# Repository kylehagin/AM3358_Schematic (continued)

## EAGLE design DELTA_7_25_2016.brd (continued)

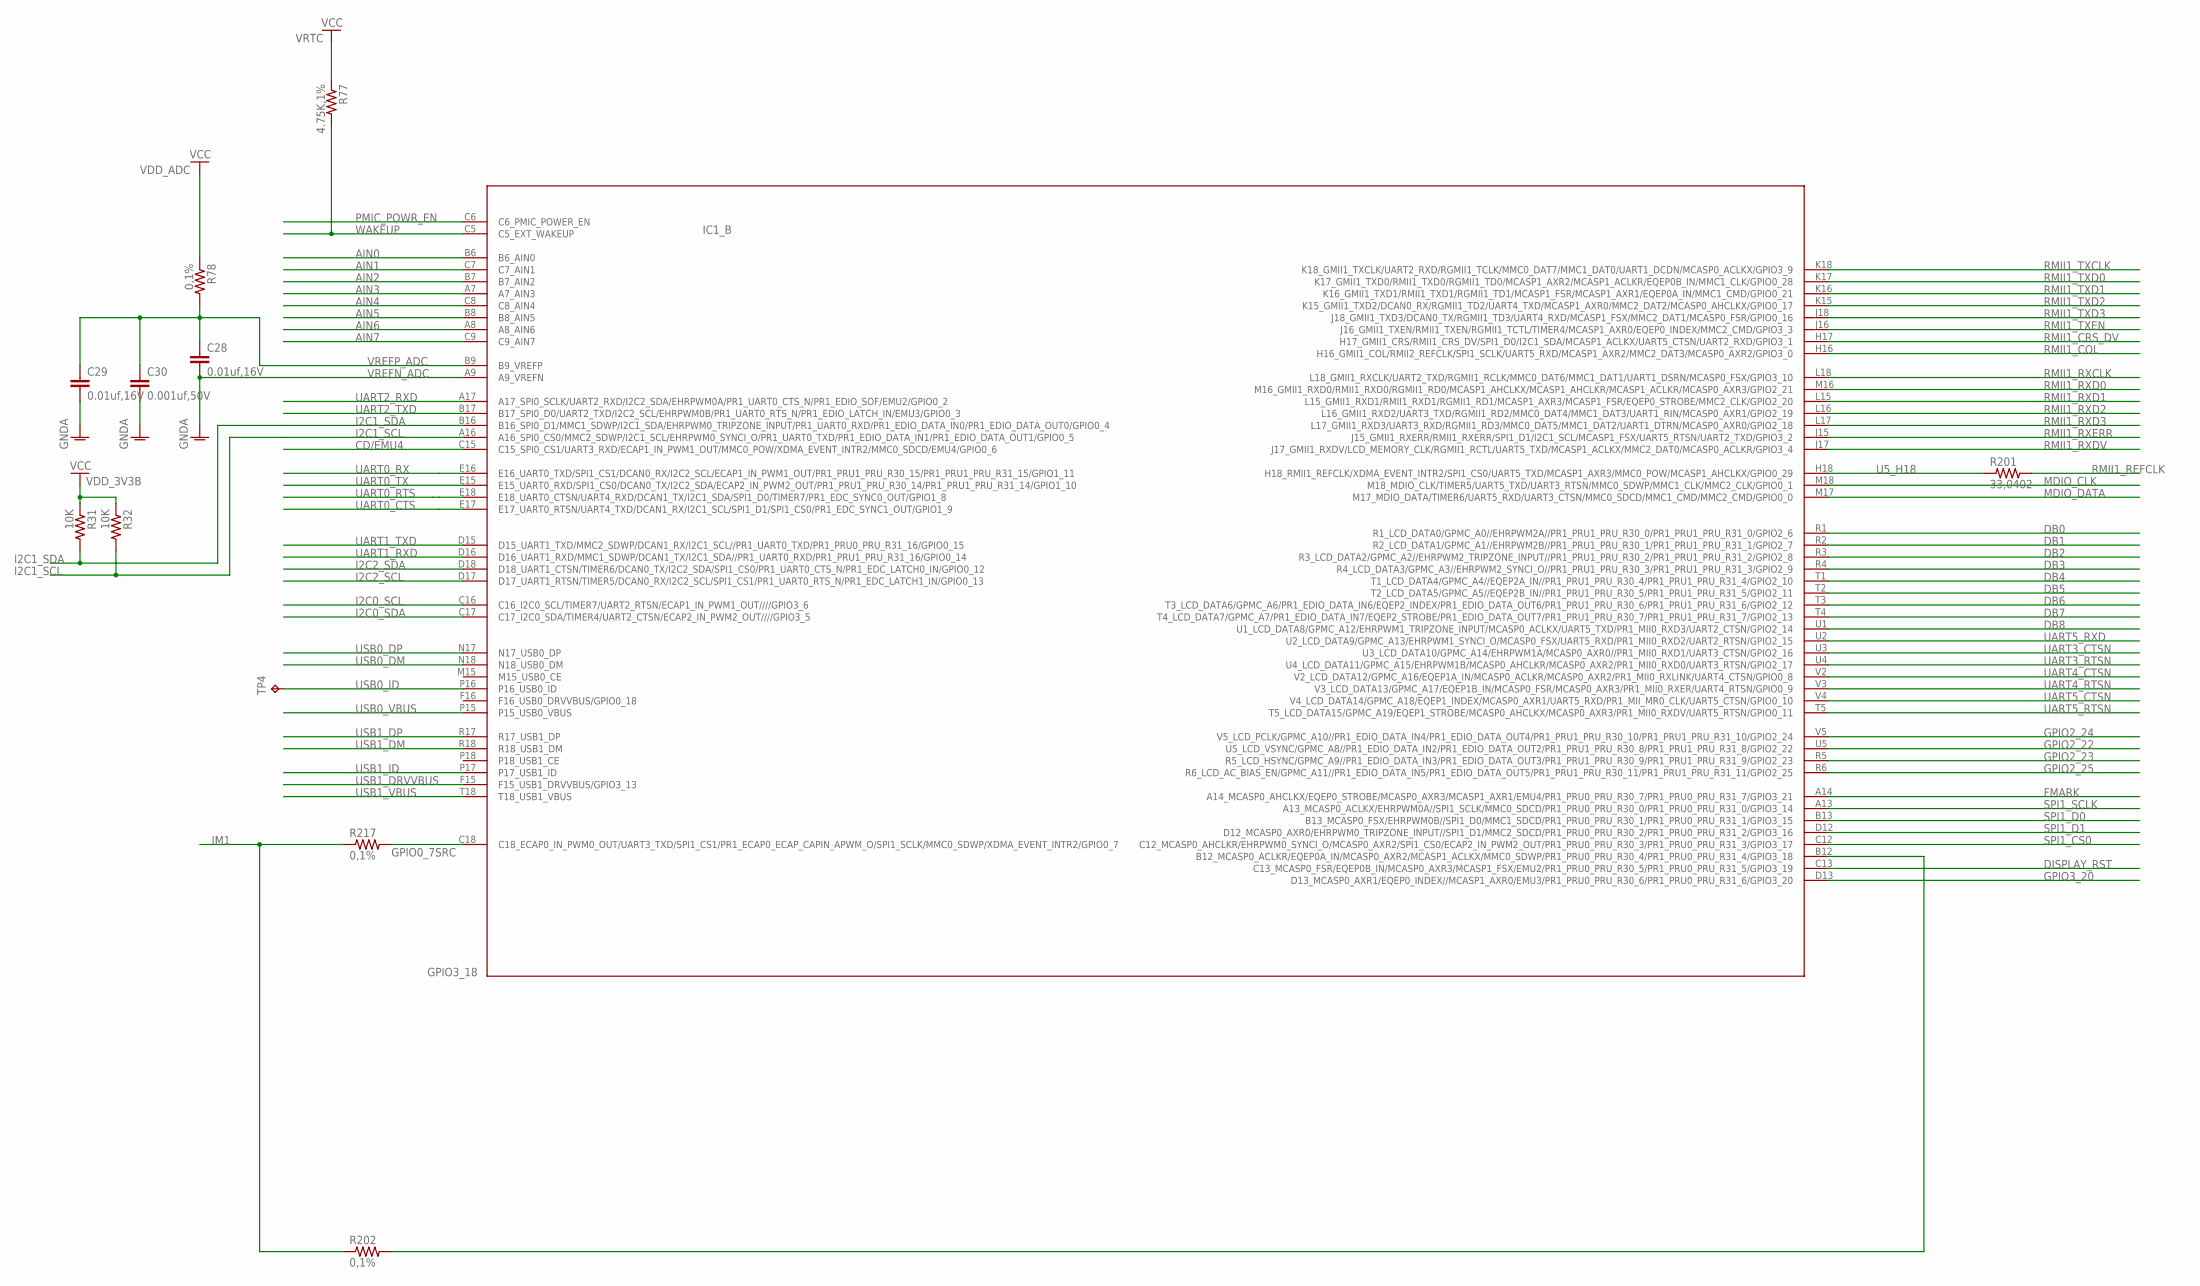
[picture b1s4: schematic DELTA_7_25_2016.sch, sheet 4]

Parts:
C28, C29: 0.01uf,16V; C0402
C30: 0.001uf,50V; C0402
IC1: AM335X_ZCZ; ZCZ_S-PBGA-N324
R31, R32: 10K; R0402
R77: 4.75K,1%; R0402
R78, R202, R217: 0,1%; R0402
R201: 33,0402; R0402
TP4: TPB1,27; B1,27

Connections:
AIN0: IC1.B6 (B6_AIN0); also elsewhere on the board
AIN1: IC1.C7 (C7_AIN1); also elsewhere on the board
AIN2: IC1.B7 (B7_AIN2); also elsewhere on the board
AIN3: IC1.A7 (A7_AIN3); also elsewhere on the board
AIN4: IC1.C8 (C8_AIN4); also elsewhere on the board
AIN5: IC1.B8 (B8_AIN5); also elsewhere on the board
AIN6: IC1.A8 (A8_AIN6); also elsewhere on the board
AIN7: IC1.C9 (C9_AIN7); also elsewhere on the board
CD/EMU4: IC1.C15 (C15_SPI0_CS1/UART3_RXD/ECAP1_IN_PWM1_OU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); also elsewhere on the board
DB0: IC1.R1 (R1_LCD_DATA0/GPMC_A0//EHRPWM2A//PR1_PRU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); also elsewhere on the board
DB1: IC1.R2 (R2_LCD_DATA1/GPMC_A1//EHRPWM2B//PR1_PRU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); also elsewhere on the board
DB2: IC1.R3 (R3_LCD_DATA2/GPMC_A2//EHRPWM2_TRIPZONE_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); also elsewhere on the board
DB3: IC1.R4 (R4_LCD_DATA3/GPMC_A3//EHRPWM2_SYNCI_O//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); also elsewhere on the board
DB4: IC1.T1 (T1_LCD_DATA4/GPMC_A4//EQEP2A_IN//PR1_PR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); also elsewhere on the board
DB5: IC1.T2 (T2_LCD_DATA5/GPMC_A5//EQEP2B_IN//PR1_PR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); also elsewhere on the board
DB6: IC1.T3 (T3_LCD_DATA6/GPMC_A6/PR1_EDIO_DATA_IN6/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); also elsewhere on the board
DB7: IC1.T4 (T4_LCD_DATA7/GPMC_A7/PR1_EDIO_DATA_IN7/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); also elsewhere on the board
DB8: IC1.U1 (U1_LCD_DATA8/GPMC_A12/EHRPWM1_TRIPZONE_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); also elsewhere on the board
DISPLAY_RST: IC1.C13 (C13_MCASP0_FSR/EQEP0B_IN/MCASP0_AXR3/MC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); also elsewhere on the board
FMARK: IC1.A14 (A14_MCASP0_AHCLKX/EQEP0_STROBE/MCASP0_A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); also elsewhere on the board
GNDA: C29.2, C30.2; also elsewhere on the board
GPIO0_7SRC: IC1.C18 (C18_ECAP0_IN_PWM0_OUT/UART3_TXD/SPI1_CS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), R217.2
GPIO2_22: IC1.U5 (U5_LCD_VSYNC/GPMC_A8//PR1_EDIO_DATA_IN2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); also elsewhere on the board
GPIO2_23: IC1.R5 (R5_LCD_HSYNC/GPMC_A9//PR1_EDIO_DATA_IN3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); also elsewhere on the board
GPIO2_24: IC1.V5 (V5_LCD_PCLK/GPMC_A10//PR1_EDIO_DATA_IN4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); also elsewhere on the board
GPIO2_25: IC1.R6 (R6_LCD_AC_BIAS_EN/GPMC_A11//PR1_EDIO_DA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); also elsewhere on the board
GPIO3_18: IC1.B12 (B12_MCASP0_ACLKR/EQEP0A_IN/MCASP0_AXR2/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), R202.2
GPIO3_20: IC1.D13 (D13_MCASP0_AXR1/EQEP0_INDEX//MCASP1_AXR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); also elsewhere on the board
I2C0_SCL: IC1.C16 (C16_I2C0_SCL/TIMER7/UART2_RTSN/ECAP1_IN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); also elsewhere on the board
I2C0_SDA: IC1.C17 (C17_I2C0_SDA/TIMER4/UART2_CTSN/ECAP2_IN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); also elsewhere on the board
I2C1_SCL: IC1.A16 (A16_SPI0_CS0/MMC2_SDWP/I2C1_SCL/EHRPWM0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), R32.2; also elsewhere on the board
I2C1_SDA: IC1.B16 (B16_SPI0_D1/MMC1_SDWP/I2C1_SDA/EHRPWM0_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), R31.2; also elsewhere on the board
I2C2_SCL: IC1.D17 (D17_UART1_RTSN/TIMER5/DCAN0_RX/I2C2_SCL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); also elsewhere on the board
I2C2_SDA: IC1.D18 (D18_UART1_CTSN/TIMER6/DCAN0_TX/I2C2_SDA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); also elsewhere on the board
IM1: R202.1, R217.1; also elsewhere on the board
MDIO_CLK: IC1.M18 (M18_MDIO_CLK/TIMER5/UART5_TXD/UART3_RTS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); also elsewhere on the board
MDIO_DATA: IC1.M17 (M17_MDIO_DATA/TIMER6/UART5_RXD/UART3_CT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); also elsewhere on the board
PMIC_POWR_EN: IC1.C6 (C6_PMIC_POWER_EN); also elsewhere on the board
RMII1_COL: IC1.H16 (H16_GMII1_COL/RMII2_REFCLK/SPI1_SCLK/UA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); also elsewhere on the board
RMII1_CRS_DV: IC1.H17 (H17_GMII1_CRS/RMII1_CRS_DV/SPI1_D0/I2C1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); also elsewhere on the board
RMII1_REFCLK: R201.2; also elsewhere on the board
RMII1_RXCLK: IC1.L18 (L18_GMII1_RXCLK/UART2_TXD/RGMII1_RCLK/M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); also elsewhere on the board
RMII1_RXD0: IC1.M16 (M16_GMII1_RXD0/RMII1_RXD0/RGMII1_RD0/MC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); also elsewhere on the board
RMII1_RXD1: IC1.L15 (L15_GMII1_RXD1/RMII1_RXD1/RGMII1_RD1/MC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); also elsewhere on the board
RMII1_RXD2: IC1.L16 (L16_GMII1_RXD2/UART3_TXD/RGMII1_RD2/MMC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); also elsewhere on the board
RMII1_RXD3: IC1.L17 (L17_GMII1_RXD3/UART3_RXD/RGMII1_RD3/MMC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); also elsewhere on the board
RMII1_RXDV: IC1.J17 (J17_GMII1_RXDV/LCD_MEMORY_CLK/RGMII1_RC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); also elsewhere on the board
RMII1_RXERR: IC1.J15 (J15_GMII1_RXERR/RMII1_RXERR/SPI1_D1/I2C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); also elsewhere on the board
RMII1_TXCLK: IC1.K18 (K18_GMII1_TXCLK/UART2_RXD/RGMII1_TCLK/M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); also elsewhere on the board
RMII1_TXD0: IC1.K17 (K17_GMII1_TXD0/RMII1_TXD0/RGMII1_TD0/MC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); also elsewhere on the board
RMII1_TXD1: IC1.K16 (K16_GMII1_TXD1/RMII1_TXD1/RGMII1_TD1/MC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); also elsewhere on the board
RMII1_TXD2: IC1.K15 (K15_GMII1_TXD2/DCAN0_RX/RGMII1_TD2/UART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); also elsewhere on the board
RMII1_TXD3: IC1.J18 (J18_GMII1_TXD3/DCAN0_TX/RGMII1_TD3/UART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); also elsewhere on the board
RMII1_TXEN: IC1.J16 (J16_GMII1_TXEN/RMII1_TXEN/RGMII1_TCTL/T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); also elsewhere on the board
SPI1_CS0: IC1.C12 (C12_MCASP0_AHCLKR/EHRPWM0_SYNCI_O/MCASP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); also elsewhere on the board
SPI1_D0: IC1.B13 (B13_MCASP0_FSX/EHRPWM0B//SPI1_D0/MMC1_S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); also elsewhere on the board
SPI1_D1: IC1.D12 (D12_MCASP0_AXR0/EHRPWM0_TRIPZONE_INPUT/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); also elsewhere on the board
SPI1_SCLK: IC1.A13 (A13_MCASP0_ACLKX/EHRPWM0A//SPI1_SCLK/MM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); also elsewhere on the board
U5_H18: IC1.H18 (H18_RMII1_REFCLK/XDMA_EVENT_INTR2/SPI1_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), R201.1
UART0_CTS: IC1.E17 (E17_UART0_RTSN/UART4_TXD/DCAN1_RX/I2C1_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); also elsewhere on the board
UART0_RTS: IC1.E18 (E18_UART0_CTSN/UART4_RXD/DCAN1_TX/I2C1_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); also elsewhere on the board
UART0_RX: IC1.E16 (E16_UART0_TXD/SPI1_CS1/DCAN0_RX/I2C2_SC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); also elsewhere on the board
UART0_TX: IC1.E15 (E15_UART0_RXD/SPI1_CS0/DCAN0_TX/I2C2_SD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); also elsewhere on the board
UART1_RXD: IC1.D16 (D16_UART1_RXD/MMC1_SDWP/DCAN1_TX/I2C1_S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); also elsewhere on the board
UART1_TXD: IC1.D15 (D15_UART1_TXD/MMC2_SDWP/DCAN1_RX/I2C1_S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); also elsewhere on the board
UART2_RXD: IC1.A17 (A17_SPI0_SCLK/UART2_RXD/I2C2_SDA/EHRPWM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); also elsewhere on the board
UART2_TXD: IC1.B17 (B17_SPI0_D0/UART2_TXD/I2C2_SCL/EHRPWM0B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); also elsewhere on the board
UART3_CTSN: IC1.U3 (U3_LCD_DATA10/GPMC_A14/EHRPWM1A/MCASP0_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); also elsewhere on the board
UART3_RTSN: IC1.U4 (U4_LCD_DATA11/GPMC_A15/EHRPWM1B/MCASP0_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); also elsewhere on the board
UART4_CTSN: IC1.V2 (V2_LCD_DATA12/GPMC_A16/EQEP1A_IN/MCASP0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); also elsewhere on the board
UART4_RTSN: IC1.V3 (V3_LCD_DATA13/GPMC_A17/EQEP1B_IN/MCASP0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); also elsewhere on the board
UART5_CTSN: IC1.V4 (V4_LCD_DATA14/GPMC_A18/EQEP1_INDEX/MCAS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); also elsewhere on the board
UART5_RTSN: IC1.T5 (T5_LCD_DATA15/GPMC_A19/EQEP1_STROBE/MCA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); also elsewhere on the board
UART5_RXD: IC1.U2 (U2_LCD_DATA9/GPMC_A13/EHRPWM1_SYNCI_O/M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); also elsewhere on the board
USB0_DM: IC1.N18 (N18_USB0_DM); also elsewhere on the board
USB0_DP: IC1.N17 (N17_USB0_DP); also elsewhere on the board
USB0_ID: IC1.P16 (P16_USB0_ID), TP4.TP
USB0_VBUS: IC1.P15 (P15_USB0_VBUS); also elsewhere on the board
USB1_DM: IC1.R18 (R18_USB1_DM); also elsewhere on the board
USB1_DP: IC1.R17 (R17_USB1_DP); also elsewhere on the board
USB1_DRVVBUS: IC1.F15 (F15_USB1_DRVVBUS/GPIO3_13); also elsewhere on the board
USB1_ID: IC1.P17 (P17_USB1_ID); also elsewhere on the board
USB1_VBUS: IC1.T18 (T18_USB1_VBUS); also elsewhere on the board
VDD_3V3B: R31.1, R32.1; also elsewhere on the board
VDD_ADC: R78.1; also elsewhere on the board
VREFN_ADC: C28.2, IC1.A9 (A9_VREFN)
VREFP_ADC: C28.1, C29.1, C30.1, IC1.B9 (B9_VREFP), R78.2
VRTC: R77.1; also elsewhere on the board
WAKEUP: IC1.C5 (C5_EXT_WAKEUP), R77.2; also elsewhere on the board

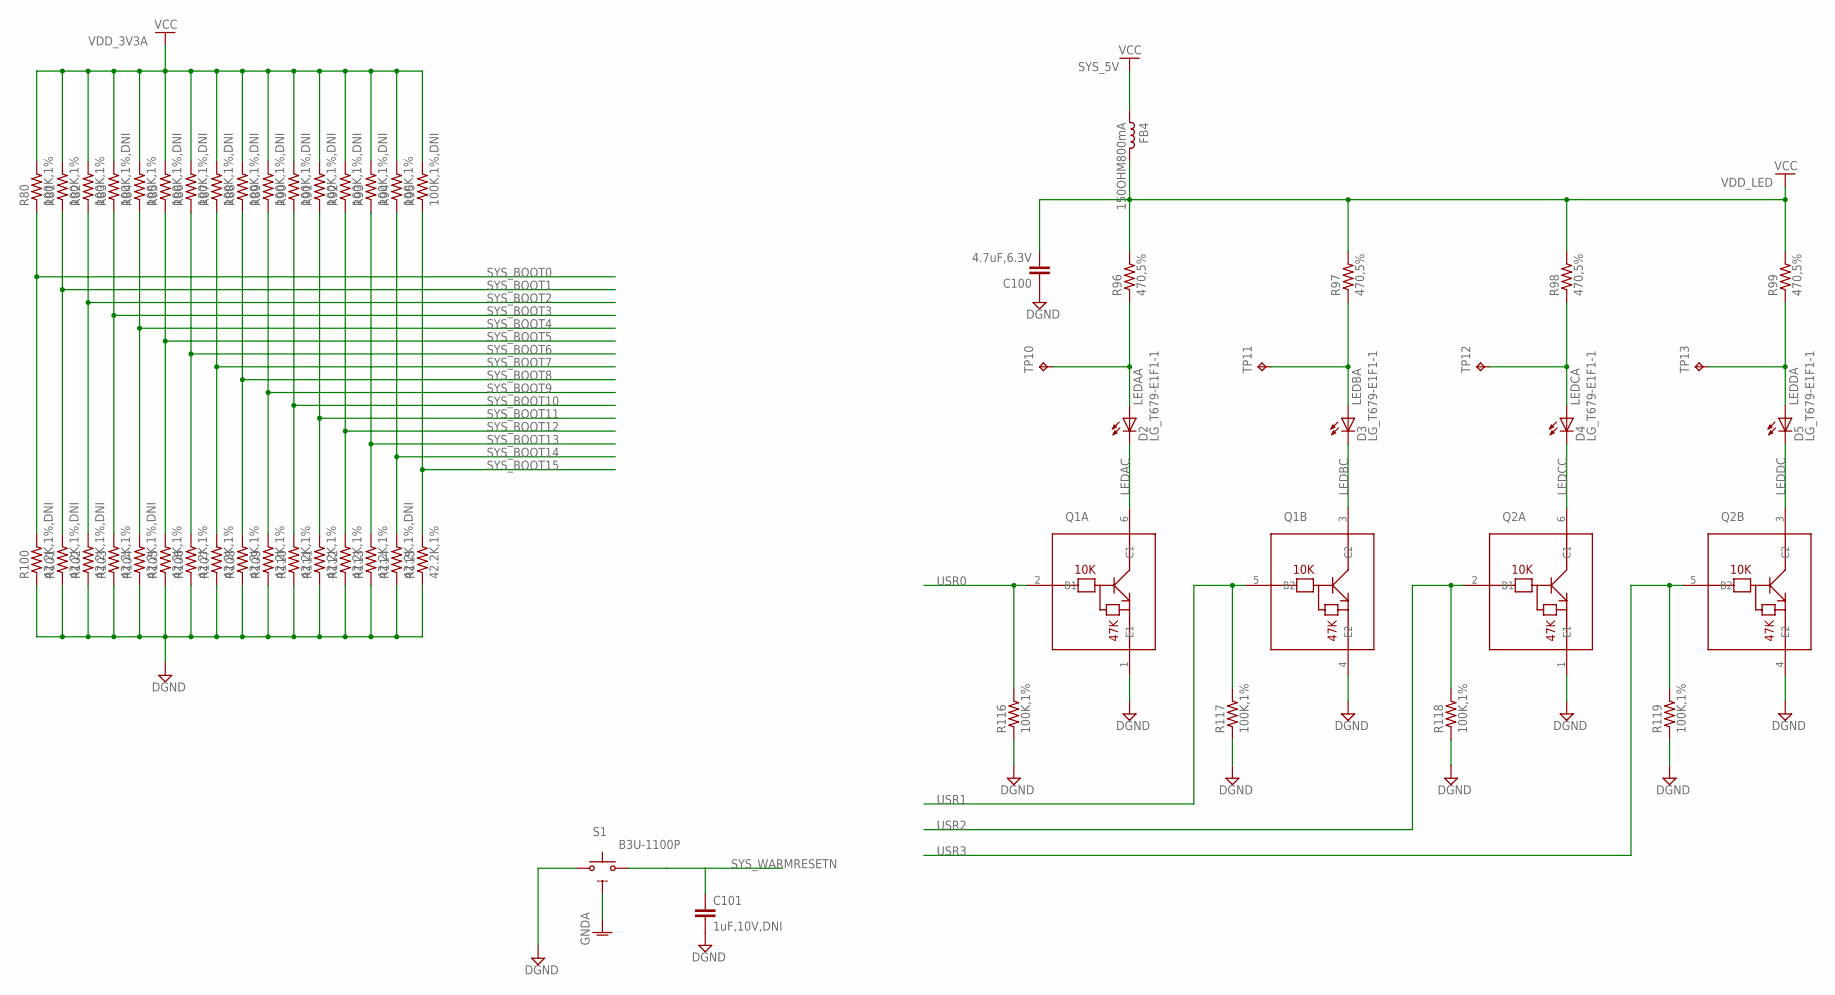
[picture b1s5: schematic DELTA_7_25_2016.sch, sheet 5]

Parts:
C100: 4.7uF,6.3V; C0402
C101: 1uF,10V,DNI; C0805
D2, D3, D4, D5: LG_T679-E1F1-1; PLCC2
FB4: 150OHM800mA; L0603
Q1, Q2: DMC56404
R80, R81, R82, R84, R94, R116, R117, R118, R119: 100K,1%; R0402
R83, R85, R86, R87, R88, R89, R90, R91, R92, R93, R95: 100K,1%,DNI; R0402
R96, R97, R98, R99: 470,5%; R0402
R100, R101, R102, R104, R114: 42.2K,1%,DNI; R0402
R103, R105, R106, R107, R108, R109, R110, R111, R112, R113, R115: 42.2K,1%; R0402
S1: B3U-1100P
TP10, TP11, TP12, TP13: TPB1,27; B1,27

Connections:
DGND: C100.1, C101.2, Q1.1 (E1), Q1.4 (E2), Q2.1 (E1), Q2.4 (E2), R100.1, R101.1, R102.1, R103.1, R104.1, R105.1, R106.1, R107.1, R108.1, R109.1, R110.1, R111.1, R112.1, R113.1, R114.1, R115.1, R116.1, R117.1, R118.1, R119.1, S1.1; also elsewhere on the board
GNDA: S1.S (G); also elsewhere on the board
LEDAA: D2.A, R96.1, TP10.TP
LEDAC: D2.C, Q1.6 (C1)
LEDBA: D3.A, R97.1, TP11.TP
LEDBC: D3.C, Q1.3 (C2)
LEDCA: D4.A, R98.1, TP12.TP
LEDCC: D4.C, Q2.6 (C1)
LEDDA: D5.A, R99.1, TP13.TP
LEDDC: D5.C, Q2.3 (C2)
SYS_5V: FB4.2; also elsewhere on the board
SYS_BOOT0: R80.1, R100.2
SYS_BOOT1: R81.1, R101.2
SYS_BOOT2: R82.1, R102.2
SYS_BOOT3: R83.1, R103.2
SYS_BOOT4: R84.1, R104.2
SYS_BOOT5: R85.1, R105.2
SYS_BOOT6: R86.1, R106.2
SYS_BOOT7: R87.1, R107.2
SYS_BOOT8: R88.1, R108.2
SYS_BOOT9: R89.1, R109.2
SYS_BOOT10: R90.1, R110.2
SYS_BOOT11: R91.1, R111.2
SYS_BOOT12: R92.1, R112.2
SYS_BOOT13: R93.1, R113.2
SYS_BOOT14: R94.1, R114.2
SYS_BOOT15: R95.1, R115.2
SYS_WARMRESETN: C101.1, S1.2 (S); also elsewhere on the board
USR0: Q1.2 (B1), R116.2; also elsewhere on the board
USR1: Q1.5 (B2), R117.2; also elsewhere on the board
USR2: Q2.2 (B1), R118.2; also elsewhere on the board
USR3: Q2.5 (B2), R119.2; also elsewhere on the board
VDD_3V3A: R80.2, R81.2, R82.2, R83.2, R84.2, R85.2, R86.2, R87.2, R88.2, R89.2, R90.2, R91.2, R92.2, R93.2, R94.2, R95.2; also elsewhere on the board
VDD_LED: C100.2, FB4.1, R96.2, R97.2, R98.2, R99.2

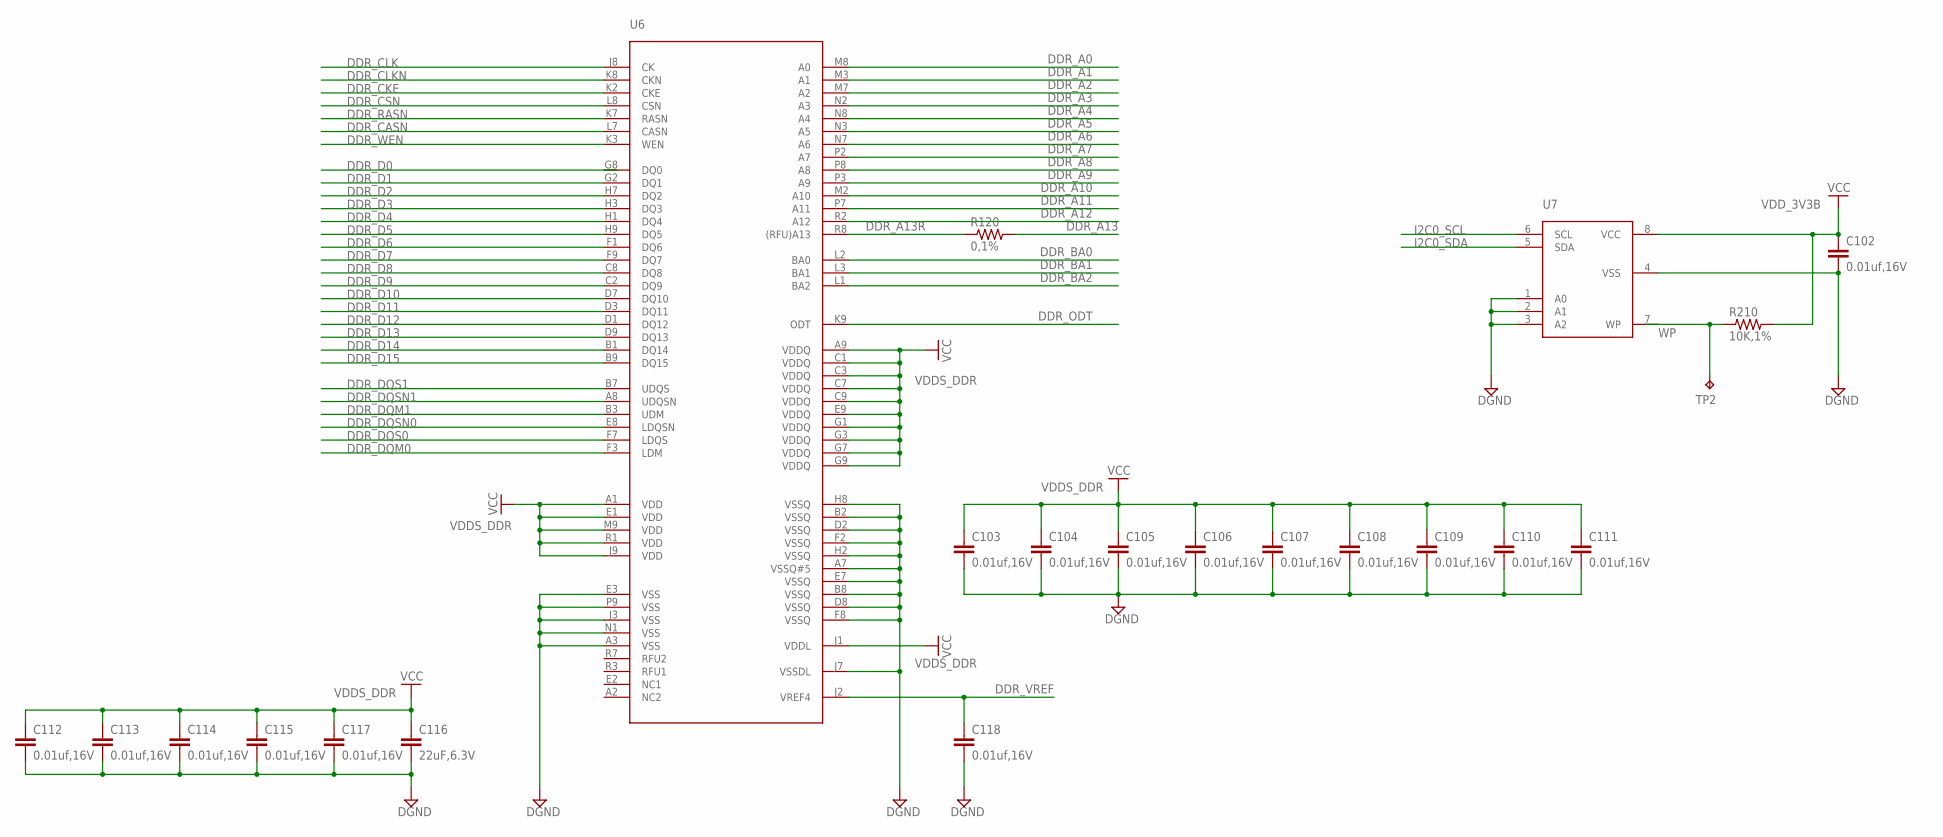
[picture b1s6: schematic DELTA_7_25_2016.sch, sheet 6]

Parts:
C102, C103, C104, C105, C106, C107, C108, C109, C110, C111, C112, C113, C114, C115, C117, C118: 0.01uf,16V; C0402
C116: 22uF,6.3V; C0402
R120: 0,1%; R0402
R210: 10K,1%; R0402
TP2: TPB1,27; B1,27
U6: MT47H128M16RT-25E:C; 90FBGA
U7: CAT24C256W; SOIC8

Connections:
DDR_A0: U6.M8 (A0); also elsewhere on the board
DDR_A1: U6.M3 (A1); also elsewhere on the board
DDR_A2: U6.M7 (A2); also elsewhere on the board
DDR_A3: U6.N2 (A3); also elsewhere on the board
DDR_A4: U6.N8 (A4); also elsewhere on the board
DDR_A5: U6.N3 (A5); also elsewhere on the board
DDR_A6: U6.N7 (A6); also elsewhere on the board
DDR_A7: U6.P2 (A7); also elsewhere on the board
DDR_A8: U6.P8 (A8); also elsewhere on the board
DDR_A9: U6.P3 (A9); also elsewhere on the board
DDR_A10: U6.M2 (A10); also elsewhere on the board
DDR_A11: U6.P7 (A11); also elsewhere on the board
DDR_A12: U6.R2 (A12); also elsewhere on the board
DDR_A13: R120.2; also elsewhere on the board
DDR_A13R: R120.1, U6.R8 ((RFU)A13)
DDR_BA0: U6.L2 (BA0); also elsewhere on the board
DDR_BA1: U6.L3 (BA1); also elsewhere on the board
DDR_BA2: U6.L1 (BA2); also elsewhere on the board
DDR_CASN: U6.L7 (CASN); also elsewhere on the board
DDR_CKE: U6.K2 (CKE); also elsewhere on the board
DDR_CLK: U6.J8 (CK); also elsewhere on the board
DDR_CLKN: U6.K8 (CKN); also elsewhere on the board
DDR_CSN: U6.L8 (CSN); also elsewhere on the board
DDR_D1: U6.G2 (DQ1); also elsewhere on the board
DDR_D2: U6.H7 (DQ2); also elsewhere on the board
DDR_D3: U6.H3 (DQ3); also elsewhere on the board
DDR_D4: U6.H1 (DQ4); also elsewhere on the board
DDR_D5: U6.H9 (DQ5); also elsewhere on the board
DDR_D6: U6.F1 (DQ6); also elsewhere on the board
DDR_D7: U6.F9 (DQ7); also elsewhere on the board
DDR_D8: U6.C8 (DQ8); also elsewhere on the board
DDR_D9: U6.C2 (DQ9); also elsewhere on the board
DDR_D10: U6.D7 (DQ10); also elsewhere on the board
DDR_D11: U6.D3 (DQ11); also elsewhere on the board
DDR_D12: U6.D1 (DQ12); also elsewhere on the board
DDR_D13: U6.D9 (DQ13); also elsewhere on the board
DDR_D14: U6.B1 (DQ14); also elsewhere on the board
DDR_D15: U6.B9 (DQ15); also elsewhere on the board
DDR_DQM0: U6.F3 (LDM); also elsewhere on the board
DDR_DQM1: U6.B3 (UDM); also elsewhere on the board
DDR_DQS0: U6.F7 (LDQS); also elsewhere on the board
DDR_DQS1: U6.B7 (UDQS); also elsewhere on the board
DDR_DQSN0: U6.E8 (LDQSN); also elsewhere on the board
DDR_DQSN1: U6.A8 (UDQSN); also elsewhere on the board
DDR_ODT: U6.K9 (ODT); also elsewhere on the board
DDR_RASN: U6.K7 (RASN); also elsewhere on the board
DDR_VREF: C118.1, U6.J2 (VREF4); also elsewhere on the board
DDR_WEN: U6.K3 (WEN); also elsewhere on the board
DGND: C102.2, C103.2, C104.2, C105.2, C106.2, C107.2, C108.2, C109.2, C110.2, C111.2, C112.2, C113.2, C114.2, C115.2, C116.2, C117.2, C118.2, U6.A3 (VSS), U6.A7 (VSSQ#5), U6.B2 (VSSQ), U6.B8 (VSSQ), U6.D2 (VSSQ), U6.D8 (VSSQ), U6.E3 (VSS), U6.E7 (VSSQ), U6.F2 (VSSQ), U6.F8 (VSSQ), U6.H2 (VSSQ), U6.H8 (VSSQ), U6.J3 (VSS), U6.J7 (VSSDL), U6.N1 (VSS), U6.P9 (VSS), U7.1 (A0), U7.2 (A1), U7.3 (A2), U7.4 (VSS); also elsewhere on the board
I2C0_SCL: U7.6 (SCL); also elsewhere on the board
I2C0_SDA: U7.5 (SDA); also elsewhere on the board
VDDS_DDR: C103.1, C104.1, C105.1, C106.1, C107.1, C108.1, C109.1, C110.1, C111.1, C112.1, C113.1, C114.1, C115.1, C116.1, C117.1, U6.A1 (VDD), U6.A9 (VDDQ), U6.C1 (VDDQ), U6.C3 (VDDQ), U6.C7 (VDDQ), U6.C9 (VDDQ), U6.E1 (VDD), U6.E9 (VDDQ), U6.G1 (VDDQ), U6.G3 (VDDQ), U6.G7 (VDDQ), U6.G9 (VDDQ), U6.J1 (VDDL), U6.J9 (VDD), U6.M9 (VDD), U6.R1 (VDD); also elsewhere on the board
VDD_3V3B: C102.1, R210.2, U7.8 (VCC); also elsewhere on the board
WP: R210.1, TP2.TP

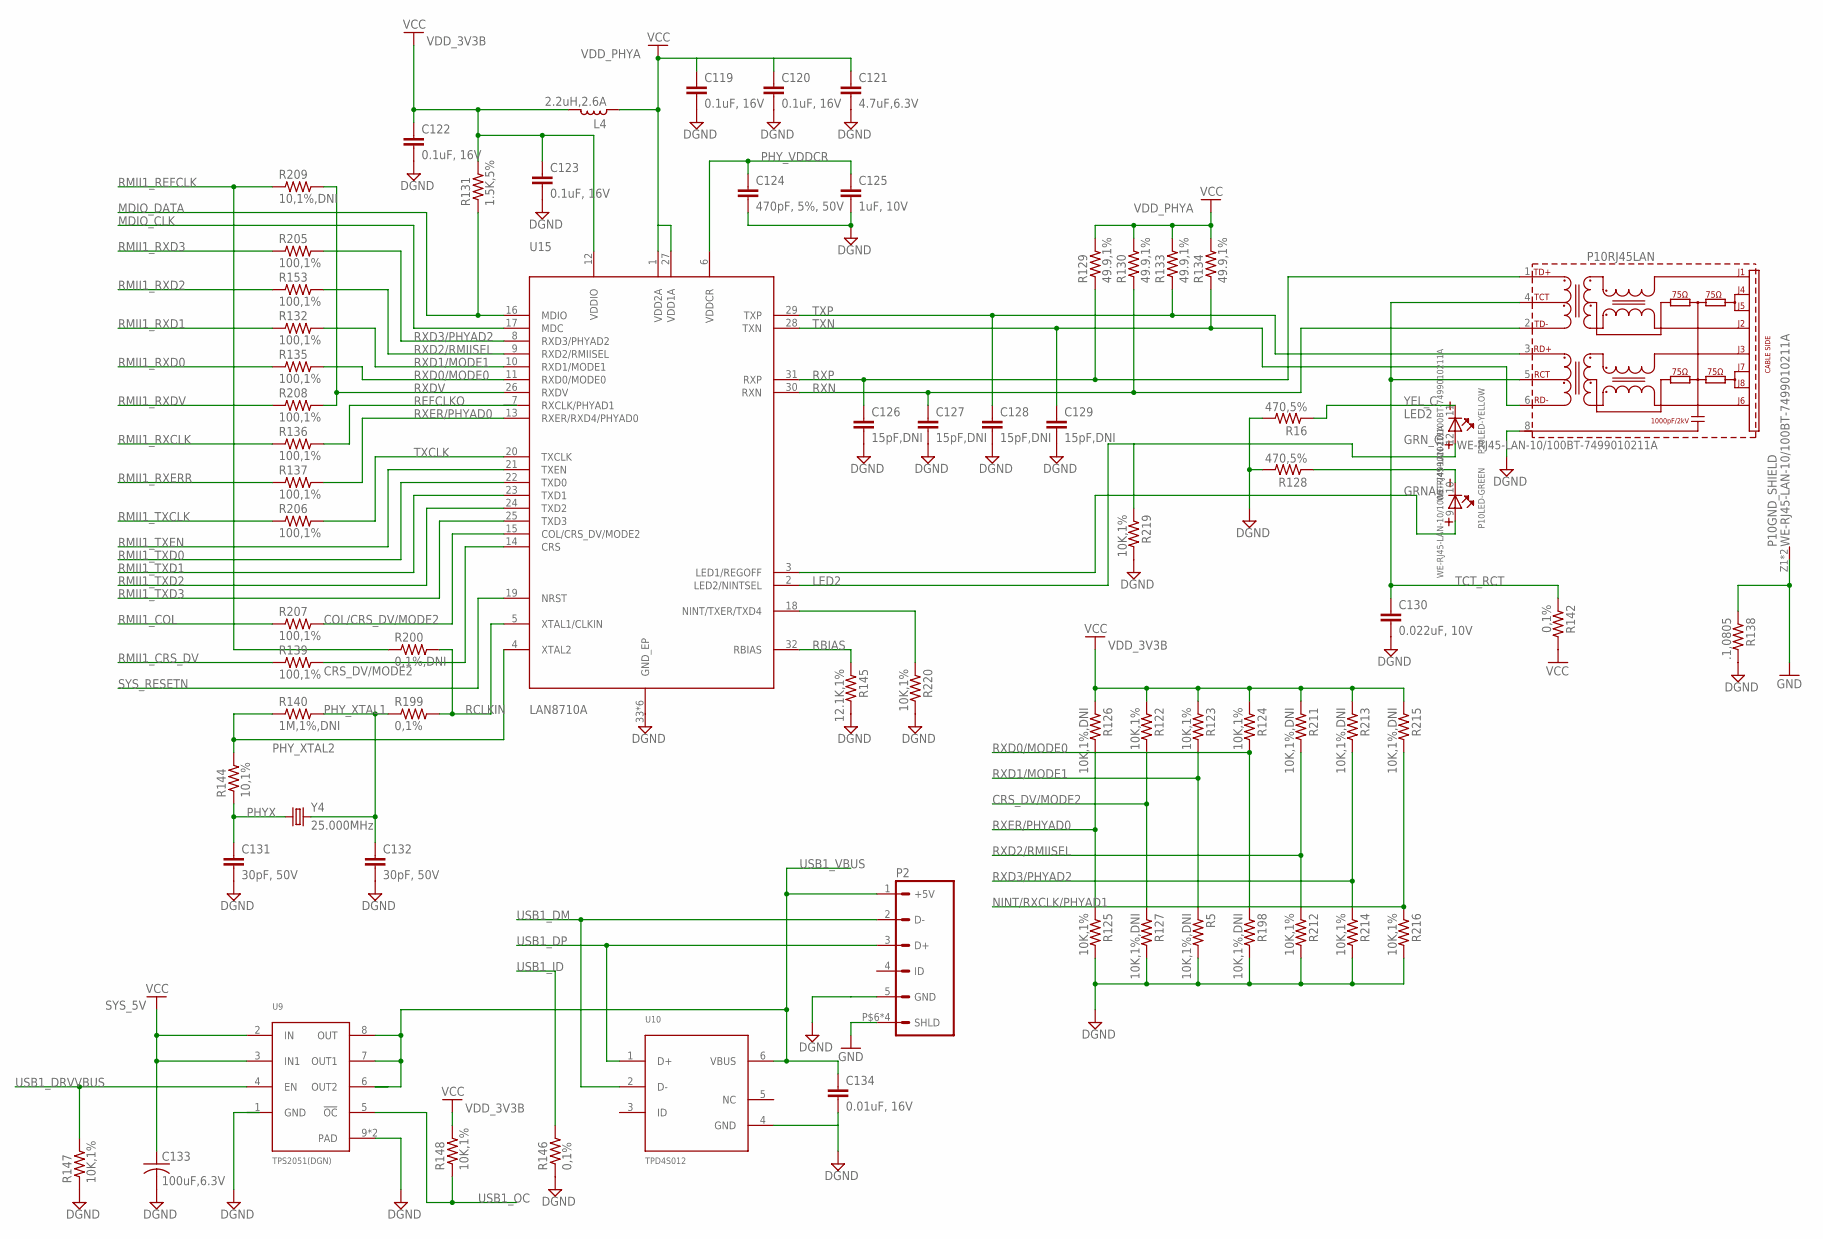
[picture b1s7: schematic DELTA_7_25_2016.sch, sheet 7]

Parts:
C119, C120, C122, C123: 0.1uF, 16V; C0402
C121: 4.7uF,6.3V; C0402
C124: 470pF, 5%, 50V; C0402
C125: 1uF, 10V; C0402
C126, C127, C128, C129: 15pF,DNI; C2.5-3
C130: 0.022uF, 10V; C0402
C131, C132: 30pF, 50V; C0402
C133: 100uF,6.3V; CAP_C
C134: 0.01uF, 16V; C0402
L4: 2.2uH,2.6A; L1008
P2: CON-MINI_USB-A; MINI-USB-A
P10: WE-RJ45-LAN-10/100BT-7499010211A; 74990-WITH-LED-TYPE2
R5, R126, R127, R198, R211, R213, R215: 10K,1%,DNI; R0402
R16, R128: 470,5%; R0402
R122, R123, R124, R125, R147, R148, R212, R214, R216, R219, R220: 10K,1%; R0402
R129, R130, R133, R134: 49.9,1%; R0402
R131: 1.5K,5%; R0402
R132, R135, R136, R137, R139, R153, R205, R206, R207, R208: 100,1%; R0402
R138: .1,0805; R0402
R140: 1M,1%,DNI; R0402
R142, R146, R199: 0,1%; R0402
R144: 10,1%; R0402
R145: 12.1K,1%; R0402
R200: 0,1%,DNI; R0402
R209: 10,1%,DNI; R0402
U9: TPS2051(DGN); DGN
U10: TPD4S012; DRY(R-PUSON-N6)
U15: LAN8710A; 32-QFN
Y4: 25.000MHz; HC49/S

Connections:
COL/CRS_DV/MODE2: R207.2, U15.15 (COL/CRS_DV/MODE2)
CRS_DV/MODE2: R122.2, R127.1, R139.2, U15.14 (CRS)
DGND: C119.2, C120.2, C121.2, C122.2, C123.2, C124.2, C125.2, C126.2, C127.2, C128.2, C129.2, C130.2, C131.2, C132.2, C133.- (2), C134.2, P2.5 (GND), P10.8 (SH), R5.2, R16.2, R125.2, R127.2, R128.2, R138.2, R145.2, R146.1, R147.1, R198.2, R212.2, R214.2, R216.2, R219.2, R220.2, U9.9 (PAD), U9.GND (PAD), U10.4 (GND), U15.33 (GND_EP), U15.W1 (GND_EP), U15.W2 (GND_EP), U15.W3 (GND_EP), U15.W4 (GND_EP), U15.W5 (GND_EP); also elsewhere on the board
GND: P2.P$6 (SHLD), P2.P$7 (SHLD), P2.P$8 (SHLD), P2.P$9 (SHLD), P10.Z1, P10.Z2, R138.1; also elsewhere on the board
GRNA: P10.9 (A), U15.3 (LED1/REGOFF)
GRN_C: P10.10 (K), R128.1
LED2: P10.12 (A), R219.1, U15.2 (LED2/NINTSEL)
MDIO_CLK: U15.17 (MDC); also elsewhere on the board
MDIO_DATA: R131.1, U15.16 (MDIO); also elsewhere on the board
unnamed: R220.1, U15.18 (NINT/TXER/TXD4)
NINT/RXCLK/PHYAD1: R215.2, R216.1
PHYX: C131.1, R144.1, Y4.1
PHY_VDDCR: C124.1, C125.1, U15.6 (VDDCR)
PHY_XTAL1: C132.1, R140.2, R199.1, Y4.2
PHY_XTAL2: R140.1, R144.2, U15.4 (XTAL2)
RBIAS: R145.1, U15.32 (RBIAS)
RCLKIN: R199.2, R200.2, U15.5 (XTAL1/CLKIN)
REFCLKO: R136.2
RMII1_COL: R207.1; also elsewhere on the board
RMII1_CRS_DV: R139.1; also elsewhere on the board
RMII1_REFCLK: R200.1, R209.1; also elsewhere on the board
RMII1_RXCLK: R136.1; also elsewhere on the board
RMII1_RXD0: R135.1; also elsewhere on the board
RMII1_RXD1: R132.1; also elsewhere on the board
RMII1_RXD2: R153.1; also elsewhere on the board
RMII1_RXD3: R205.1; also elsewhere on the board
RMII1_RXDV: R208.1; also elsewhere on the board
RMII1_RXERR: R137.1; also elsewhere on the board
RMII1_TXCLK: R206.1; also elsewhere on the board
RMII1_TXD0: U15.22 (TXD0); also elsewhere on the board
RMII1_TXD1: U15.23 (TXD1); also elsewhere on the board
RMII1_TXD2: U15.24 (TXD2); also elsewhere on the board
RMII1_TXD3: U15.25 (TXD3); also elsewhere on the board
RMII1_TXEN: U15.21 (TXEN); also elsewhere on the board
RXD0/MODE0: R124.2, R135.2, R198.1, U15.11 (RXD0/MODE0)
RXD1/MODE1: R5.1, R123.2, R132.2, U15.10 (RXD1/MODE1)
RXD2/RMIISEL: R153.2, R211.2, R212.1, U15.9 (RXD2/RMIISEL)
RXD3/PHYAD2: R205.2, R213.2, R214.1, U15.8 (RXD3/PHYAD2)
RXDV: R208.2, R209.2, U15.26 (RXDV)
RXER/PHYAD0: R125.1, R126.2, R137.2, U15.13 (RXER/RXD4/PHYAD0)
RXN: C127.1, P10.2 (TD-), R130.1, U15.30 (RXN)
RXP: C126.1, P10.1 (TD+), R129.1, U15.31 (RXP)
SYS_5V: C133.+ (1), U9.2 (IN), U9.3 (IN1); also elsewhere on the board
SYS_RESETN: U15.19 (NRST); also elsewhere on the board
TCT_RCT: C130.1, P10.4 (TCT), P10.5 (RCT), R142.1
TXCLK: R206.2, U15.20 (TXCLK)
TXN: C129.1, P10.6 (RD-), R134.1, U15.28 (TXN)
TXP: C128.1, P10.3 (RD+), R133.1, U15.29 (TXP)
USB1_DM: P2.2 (D-), U10.2 (D-); also elsewhere on the board
USB1_DP: P2.3 (D+), U10.1 (D+); also elsewhere on the board
USB1_DRVVBUS: R147.2, U9.4 (EN); also elsewhere on the board
USB1_ID: R146.2; also elsewhere on the board
USB1_OC: R148.1, U9.5 (!OC); also elsewhere on the board
USB1_VBUS: C134.1, P2.1 (+5V), U9.6 (OUT2), U9.7 (OUT1), U9.8 (OUT), U10.6 (VBUS); also elsewhere on the board
VCC: R142.2; also elsewhere on the board
VDD_3V3B: C122.1, C123.1, L4.1, R122.1, R123.1, R124.1, R126.1, R131.2, R148.2, R211.1, R213.1, R215.1, U15.12 (VDDIO); also elsewhere on the board
VDD_PHYA: C119.1, C120.1, C121.1, L4.2, R129.2, R130.2, R133.2, R134.2, U15.1 (VDD2A), U15.27 (VDD1A)
YEL_C: P10.11 (K), R16.1

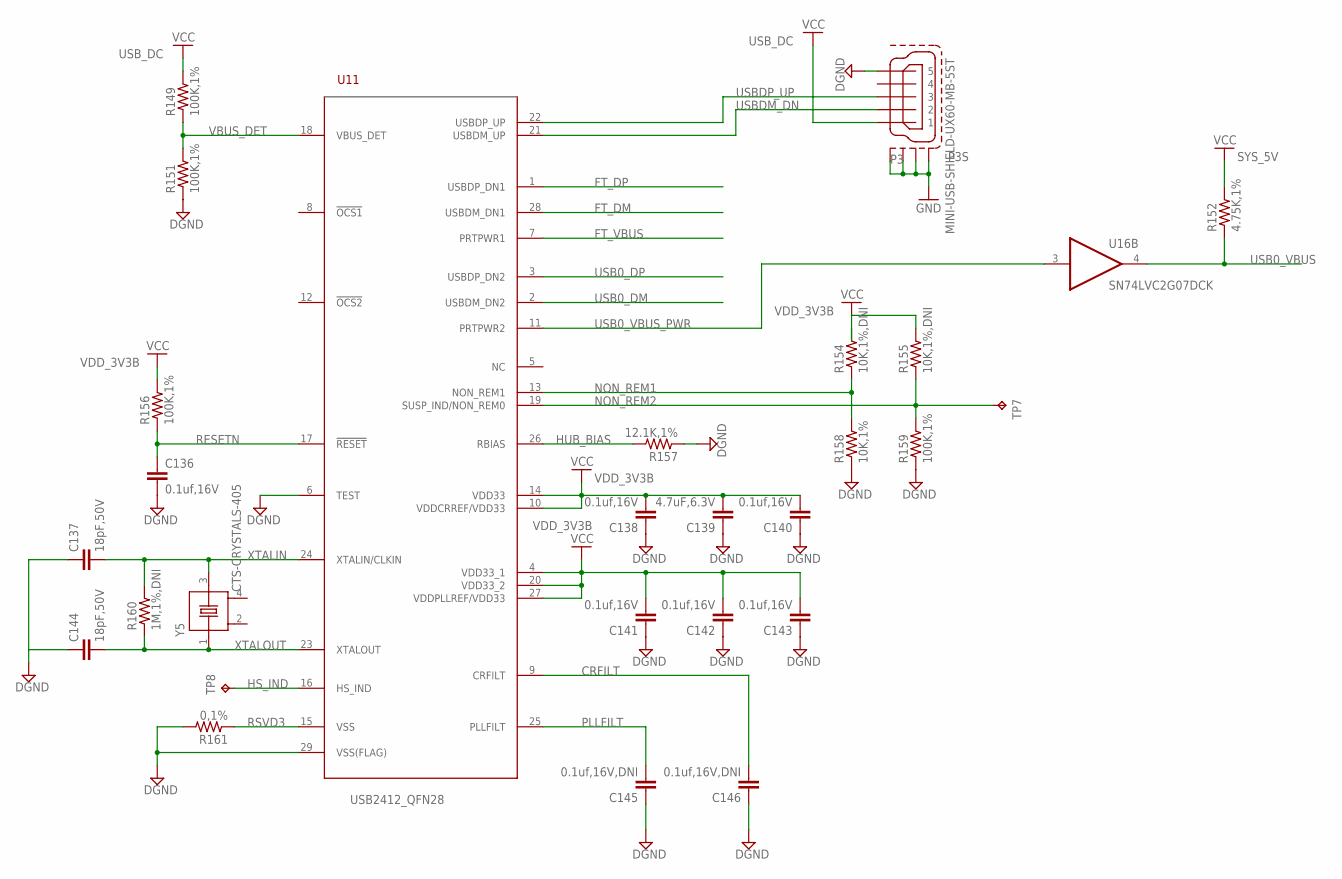
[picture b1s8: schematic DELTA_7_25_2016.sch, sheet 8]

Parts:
C136, C138, C140, C141, C142, C143: 0.1uf,16V; C402
C137, C144: 18pF,50V; C402
C139: 4.7uF,6.3V; C402
C145, C146: 0.1uf,16V,DNI; C805
P3: MINI-USB-SHIELD-UX60-MB-5ST; UX60-MB-5ST
R149, R151, R156, R159: 100K,1%; R0402
R152: 4.75K,1%; R0402
R154, R155: 10K,1%,DNI; R0402
R157: 12.1K,1%; R0402
R158: 10K,1%; R0402
R160: 1M,1%,DNI; R0402
R161: 0,1%; R0402
TP7, TP8: TPB1,27; B1,27
U11: USB2412_QFN28; QFN28
U16: SN74LVC2G07DCK; DCK(R-PDSO-G6)
Y5: CTS-CRYSTALS-405; CTS-405

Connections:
CRFILT: C146.2, U11.9 (CRFILT)
DGND: C136.2, C137.1, C138.1, C139.1, C140.1, C141.1, C142.1, C143.1, C144.1, C145.1, C146.1, P3.5, R151.1, R157.1, R158.1, R159.1, R161.2, U11.6 (TEST), U11.29 (VSS(FLAG)); also elsewhere on the board
FT_DM: U11.28 (USBDM_DN1); also elsewhere on the board
FT_DP: U11.1 (USBDP_DN1); also elsewhere on the board
FT_VBUS: U11.7 (PRTPWR1); also elsewhere on the board
GND: P3.M1 (S1), P3.M2 (S2), P3.M3 (S3), P3.M4 (S4); also elsewhere on the board
HS_IND: TP8.TP, U11.16 (HS_IND)
HUB_BIAS: R157.2, U11.26 (RBIAS)
NON_REM1: R154.1, R158.2, U11.13 (NON_REM1)
NON_REM2: R155.1, R159.2, TP7.TP, U11.19 (SUSP_IND/NON_REM0)
PLLFILT: C145.2, U11.25 (PLLFILT)
RESETN: C136.1, R156.1, U11.17 (!RESET)
RSVD3: R161.1, U11.15 (VSS)
SYS_5V: R152.2; also elsewhere on the board
USB0_DM: U11.2 (USBDM_DN2); also elsewhere on the board
USB0_DP: U11.3 (USBDP_DN2); also elsewhere on the board
USB0_VBUS: R152.1, U16.4 (O); also elsewhere on the board
USB0_VBUS_PWR: U11.11 (PRTPWR2), U16.3 (I)
USBDM_DN: P3.2, U11.21 (USBDM_UP)
USBDP_UP: P3.3, U11.22 (USBDP_UP)
USB_DC: P3.1, R149.2; also elsewhere on the board
VBUS_DET: R149.1, R151.2, U11.18 (VBUS_DET)
VDD_3V3B: C138.2, C139.2, C140.2, C141.2, C142.2, C143.2, R155.2, R156.2, U11.4 (VDD33_1), U11.10 (VDDCRREF/VDD33), U11.14 (VDD33), U11.20 (VDD33_2), U11.27 (VDDPLLREF/VDD33); also elsewhere on the board
XTALIN: C137.2, R160.2, U11.24 (XTALIN/CLKIN), Y5.3
XTALOUT: C144.2, R160.1, U11.23 (XTALOUT), Y5.1
